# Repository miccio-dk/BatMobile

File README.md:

# BatMobile

Sensors-enabled line-following robot. 
It can be monitored, configured, and controlled remotely using a custom-made Java software (not included in this repository).

Developed as part of a DTU Diplom 4th semester multidisciplinary project.

[Link of test-run video (hosted on YouTube)](http://youtu.be/BTn029kNY_Q)

## Installation

1. Print the PCBs (a breadboard will do too)
2. Cut the chassis pieces
3. Upload the code
4. Assemble everything
5. Run!

## Usage

TODO: Write usage instructions

## Contributing

1. Fork it!
2. Create your feature branch: `git checkout -b my-new-feature`
3. Commit your changes: `git commit -am 'Add some feature'`
4. Push to the branch: `git push origin my-new-feature`
5. Submit a pull request :D

## History

TODO: Write history

## License

Code released under the terms of GPL v3 or higher.

Other documentation licensed under Creative Commons (BY-NC-ND v3).

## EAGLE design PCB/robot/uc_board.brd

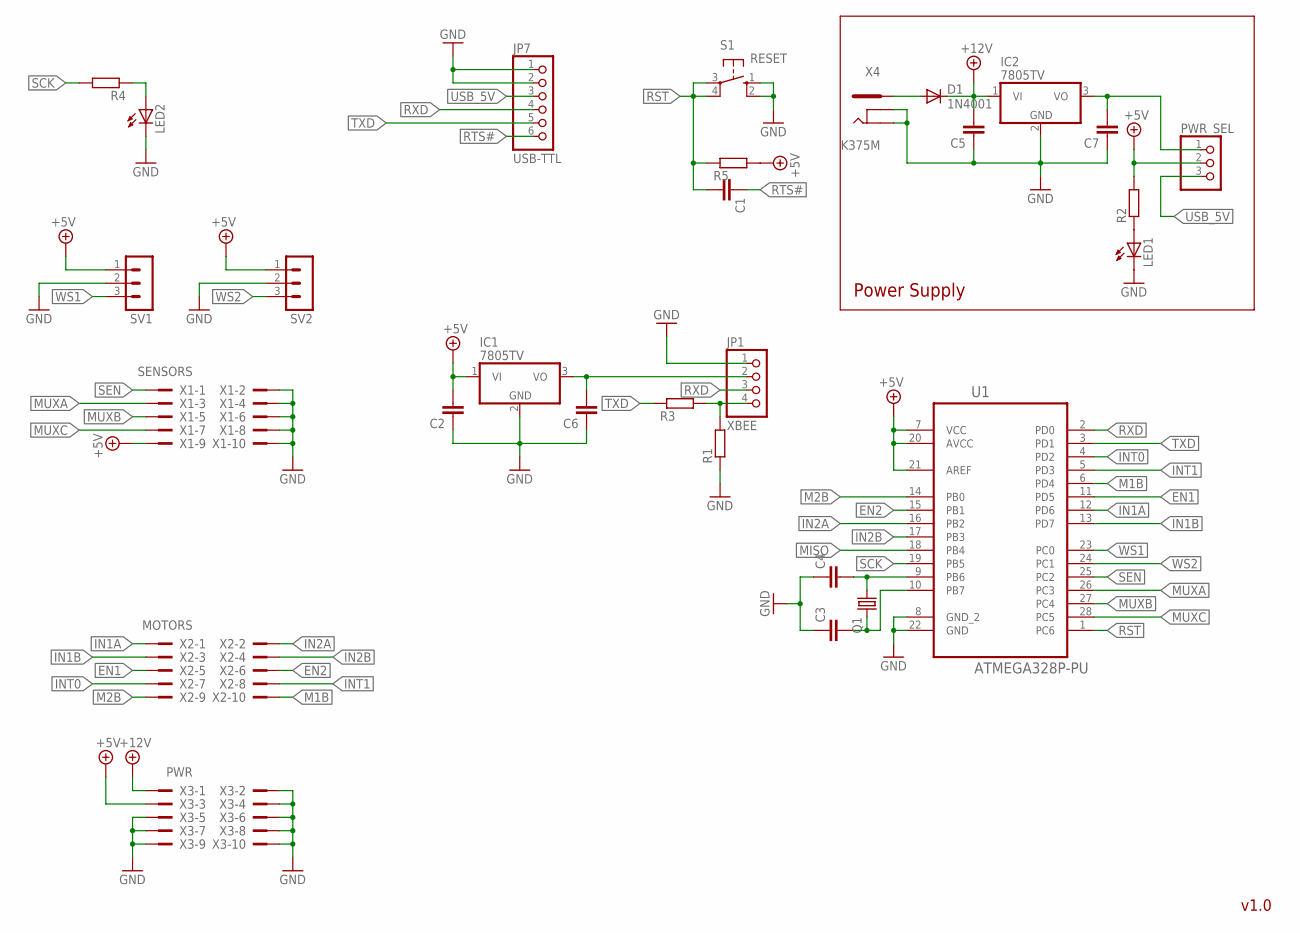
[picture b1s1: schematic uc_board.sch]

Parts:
C1: C-EU050-025X075; C050-025X075
C2, C5, C6, C7: C-EU025-050X050; C025-050X050
C3, C4: C-EU050-024X044; C050-024X044
D1: 1N4001; DO41-10
IC1, IC2: 7805TV; TO220V
JP1: XBEE; 1X04/90
JP7: USB-TTL; 1X06/90
LED1, LED2: LED5MM
PWR_SEL: PINHD-1X3; 1X03
Q1: CRYSTALHC49S; HC49/S
R1, R2, R3, R4, R5: R-EU_0207/10; 0207/10
S1: RESET; B3F-10XX
SV1, SV2: MA03-1
U1: ATMEGA328P-PU; DIP254P762X457-28
X1: SENSORS; PAK100/2500-10
X2: MOTORS; PAK100/2500-10
X3: PWR; PAK100/2500-10
X4: K375M

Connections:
+5V: C2.2, IC1.1 (VI), PWR_SEL.2, R2.2, R5.2, SV1.1, SV2.1, U1.7 (VCC), U1.20 (AVCC), U1.21 (AREF), X1.9, X3.3
+12V: C5.2, D1.C, IC2.1 (VI), X3.1
EN1: U1.11 (PD5), X2.5
EN2: U1.15 (PB1), X2.6
GND: C2.1, C3.1, C4.1, C5.1, C6.1, C7.1, IC1.2 (GND), IC2.2 (GND), JP1.1, JP7.1, JP7.2, LED1.K (C), LED2.K (C), R1.1, S1.1 (S), S1.2 (S1), SV1.2, SV2.2, U1.8 (GND_2), U1.22 (GND), X1.2, X1.4, X1.6, X1.8, X1.10, X3.2, X3.4, X3.5, X3.6, X3.7, X3.8, X3.9, X3.10, X4.2, X4.3
IN1A: U1.12 (PD6), X2.1
IN1B: U1.13 (PD7), X2.3
IN2A: U1.16 (PB2), X2.2
IN2B: U1.17 (PB3), X2.4
INT0: U1.4 (PD2), X2.7
INT1: U1.5 (PD3), X2.8
M1B: U1.6 (PD4), X2.10
M2B: U1.14 (PB0), X2.9
MISO: U1.18 (PB4)
MUXA: U1.26 (PC3), X1.3
MUXB: U1.27 (PC4), X1.5
MUXC: U1.28 (PC5), X1.7
unnamed: C4.2, Q1.1, U1.9 (PB6)
unnamed: C3.2, Q1.2, U1.10 (PB7)
unnamed: LED1.A, R2.1
unnamed: LED2.A, R4.1
unnamed: C6.2, IC1.3 (VO), JP1.2
unnamed: JP1.4, R1.2, R3.2
unnamed: D1.A, X4.1
unnamed: C7.2, IC2.3 (VO), PWR_SEL.1
RST: C1.2, R5.1, S1.3, S1.4 (P1), U1.1 (PC6)
RTS#: C1.1, JP7.6
RXD: JP1.3, JP7.4, U1.2 (PD0)
SCK: R4.2, U1.19 (PB5)
SEN: U1.25 (PC2), X1.1
TXD: JP7.5, R3.1, U1.3 (PD1)
USB_5V: JP7.3, PWR_SEL.3
WS1: SV1.3, U1.23 (PC0)
WS2: SV2.3, U1.24 (PC1)

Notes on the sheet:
Power Supply
v1.0

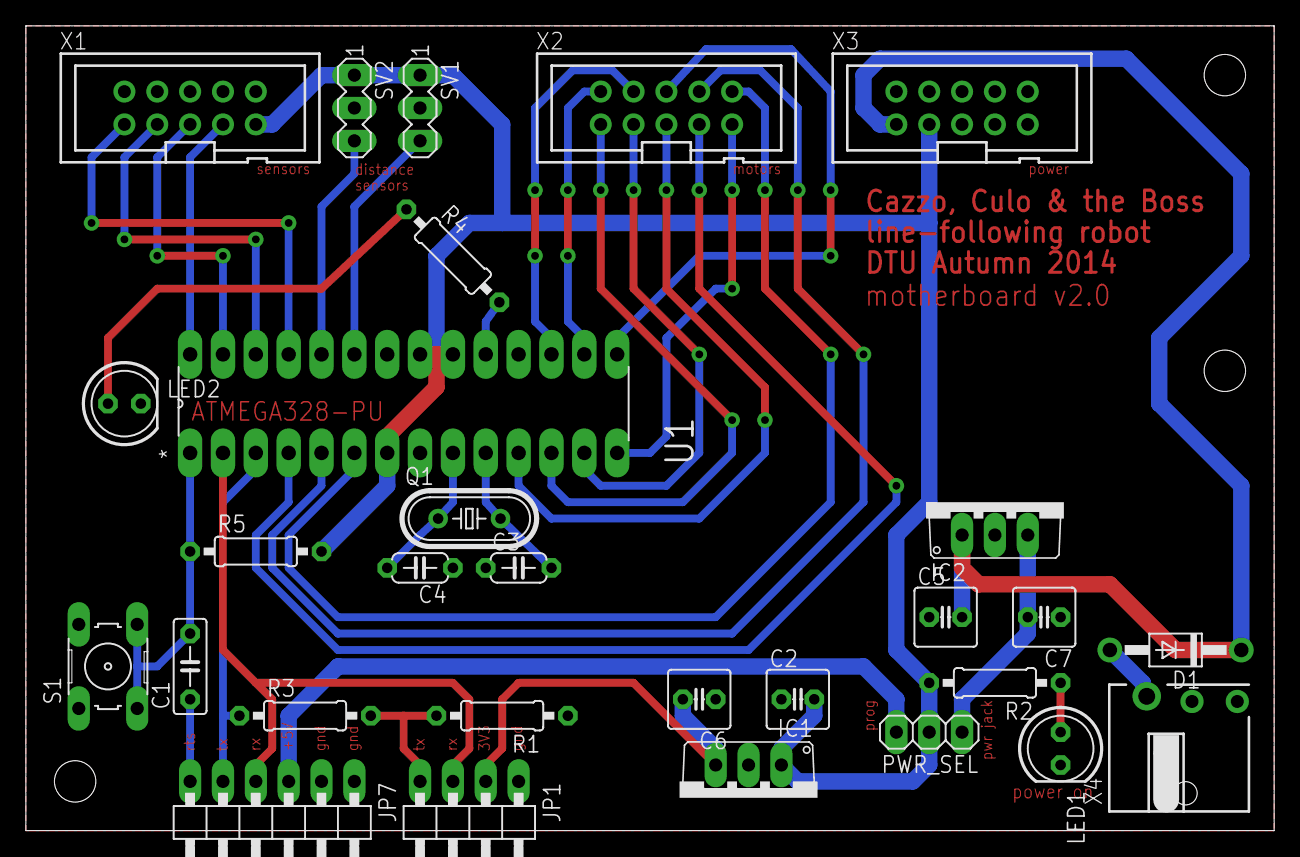
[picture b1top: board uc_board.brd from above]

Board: 2 copper layers, 96.5 x 62.2 mm, 29 parts (0 on the bottom side), 33 nets.

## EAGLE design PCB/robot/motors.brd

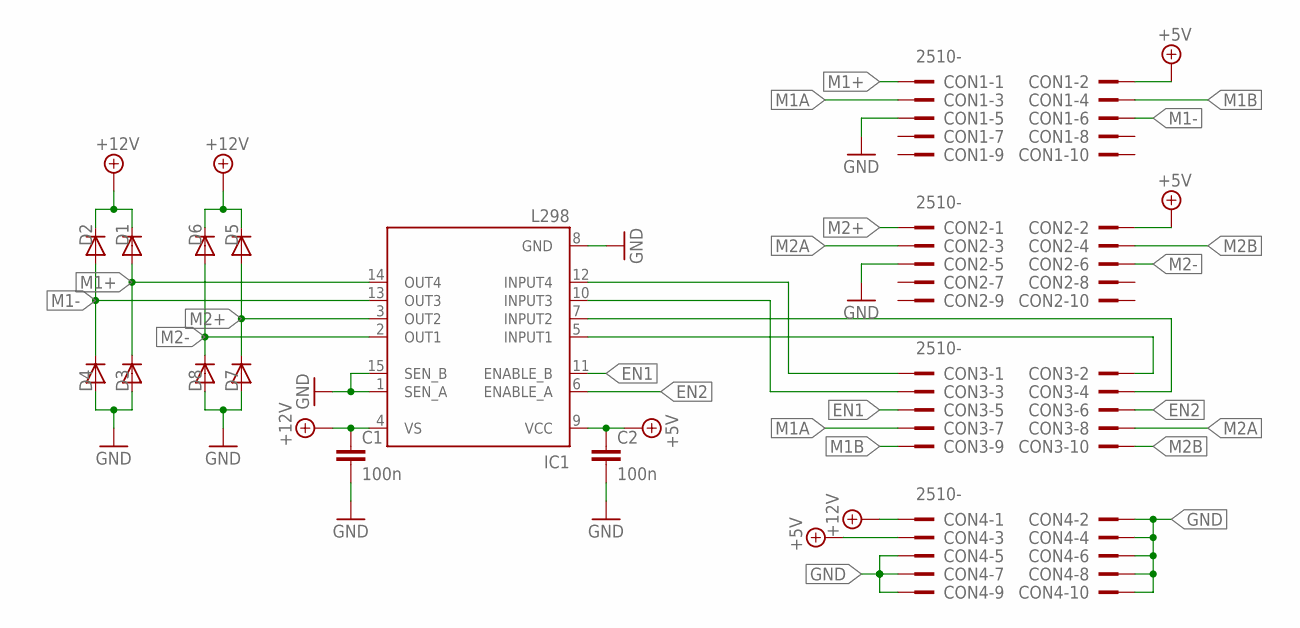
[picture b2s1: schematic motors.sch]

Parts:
C1, C2: 100n; C050-025X075
CON1, CON2, CON3, CON4: 2510-; PAK100/2500-10
D1, D2, D3, D4, D5, D6, D7, D8: 1N4004; DO41-10
IC1: L298; MULTIWATT-15

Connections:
+5V: C2.1, CON1.2, CON2.2, CON4.3, IC1.9 (VCC)
+12V: C1.1, CON4.1, D1.C, D2.C, D5.C, D6.C, IC1.4 (VS)
EN1: CON3.5, IC1.11 (ENABLE_B)
EN2: CON3.6, IC1.6 (ENABLE_A)
GND: C1.2, C2.2, CON1.5, CON2.5, CON4.2, CON4.4, CON4.5, CON4.6, CON4.7, CON4.8, CON4.9, CON4.10, D3.A, D4.A, D7.A, D8.A, IC1.1 (SEN_A), IC1.8 (GND), IC1.15 (SEN_B)
M1+: CON1.1, D1.A, D3.C, IC1.14 (OUT4)
M1-: CON1.6, D2.A, D4.C, IC1.13 (OUT3)
M1A: CON1.3, CON3.7
M1B: CON1.4, CON3.9
M2+: CON2.1, D5.A, D7.C, IC1.3 (OUT2)
M2-: CON2.6, D6.A, D8.C, IC1.2 (OUT1)
M2A: CON2.3, CON3.8
M2B: CON2.4, CON3.10
unnamed: CON3.3, IC1.10 (INPUT3)
unnamed: CON3.2, IC1.5 (INPUT1)
unnamed: CON3.1, IC1.12 (INPUT4)
unnamed: CON3.4, IC1.7 (INPUT2)

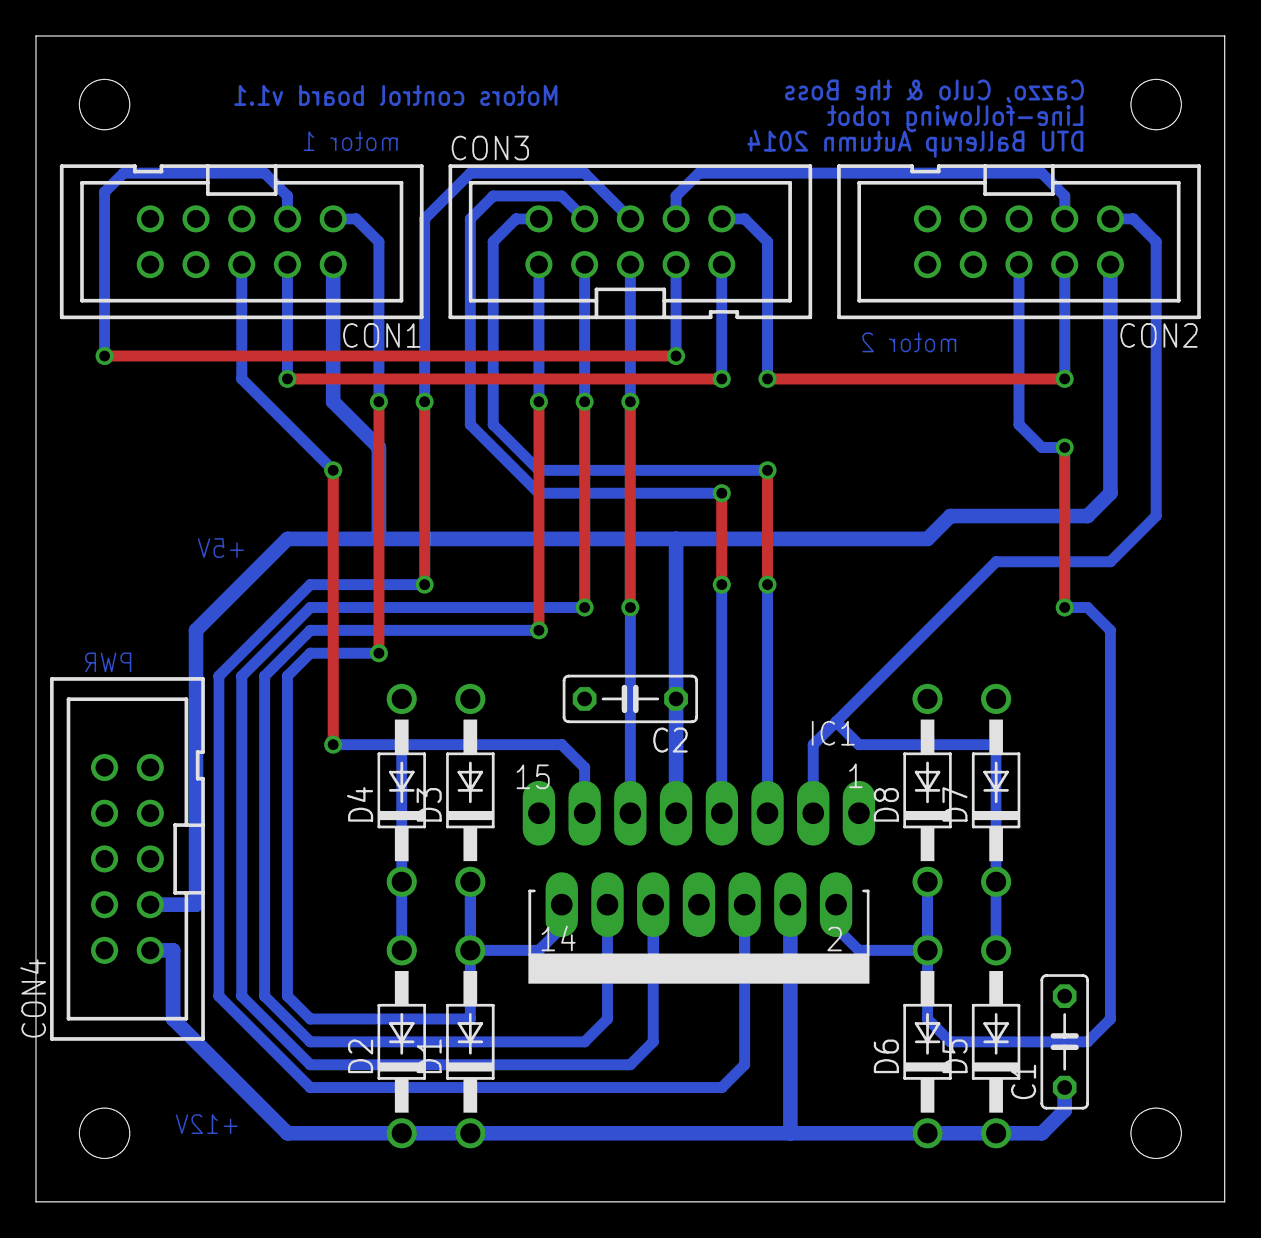
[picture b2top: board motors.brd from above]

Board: 2 copper layers, 66.0 x 64.8 mm, 15 parts (0 on the bottom side), 17 nets.

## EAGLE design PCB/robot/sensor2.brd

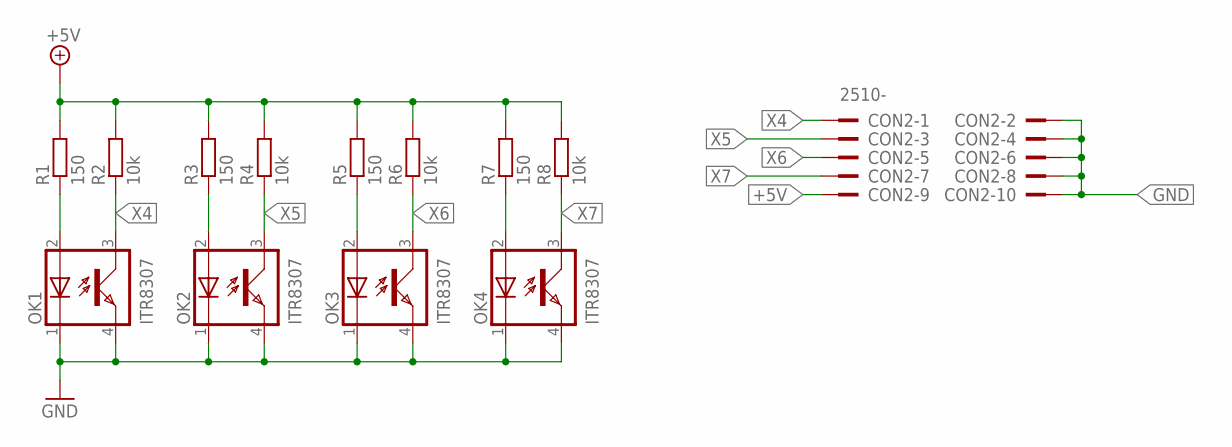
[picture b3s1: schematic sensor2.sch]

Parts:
CON2: 2510-; PAK100/2500-10
OK1, OK2, OK3, OK4: ITR8307; F43
R1, R3, R5, R7: 150; 0204/7
R2, R4, R6, R8: 10k; 0204/7

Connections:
+5V: CON2.9, R1.2, R2.2, R3.2, R4.2, R5.2, R6.2, R7.2, R8.2
GND: CON2.2, CON2.4, CON2.6, CON2.8, CON2.10, OK1.1 (C), OK1.4 (EMIT), OK2.1 (C), OK2.4 (EMIT), OK3.1 (C), OK3.4 (EMIT), OK4.1 (C), OK4.4 (EMIT)
unnamed: OK1.2 (A), R1.1
unnamed: OK2.2 (A), R3.1
unnamed: OK3.2 (A), R5.1
unnamed: OK4.2 (A), R7.1
X4: CON2.1, OK1.3 (COL), R2.1
X5: CON2.3, OK2.3 (COL), R4.1
X6: CON2.5, OK3.3 (COL), R6.1
X7: CON2.7, OK4.3 (COL), R8.1

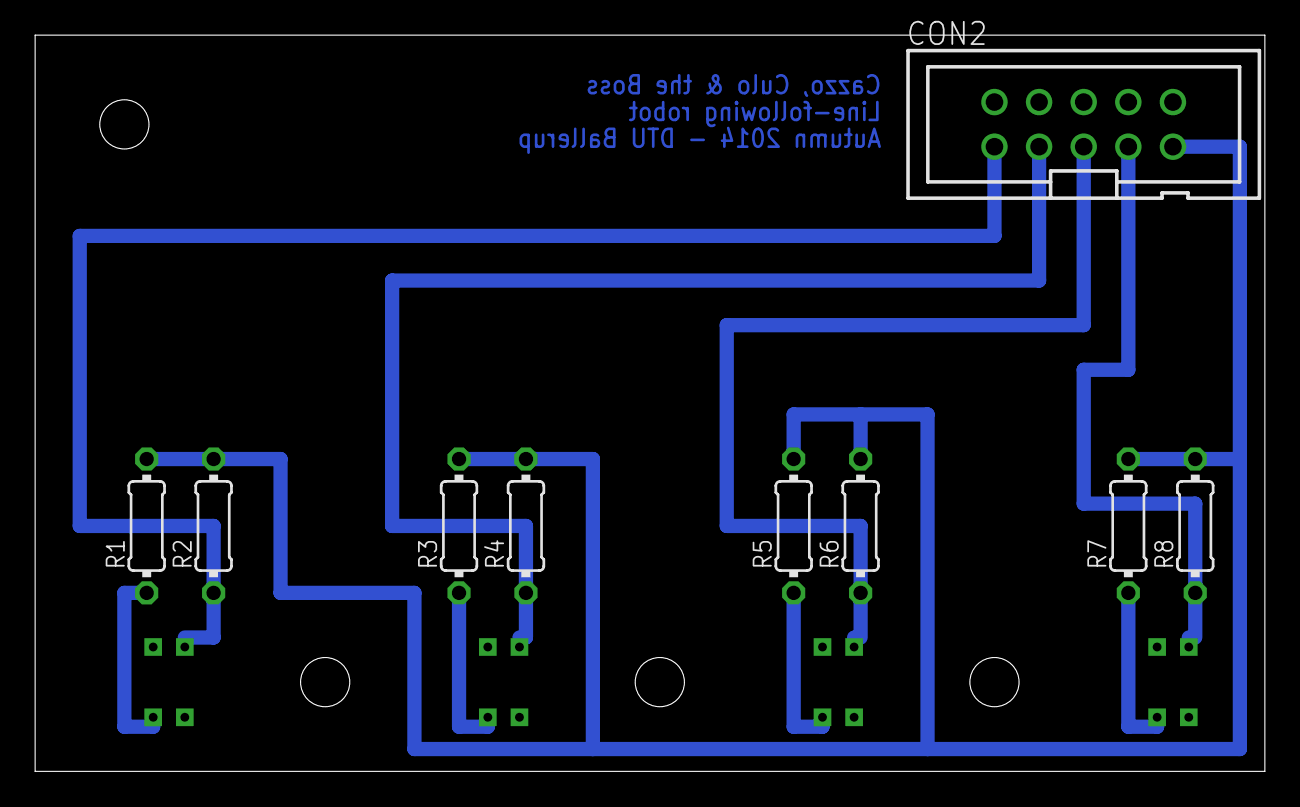
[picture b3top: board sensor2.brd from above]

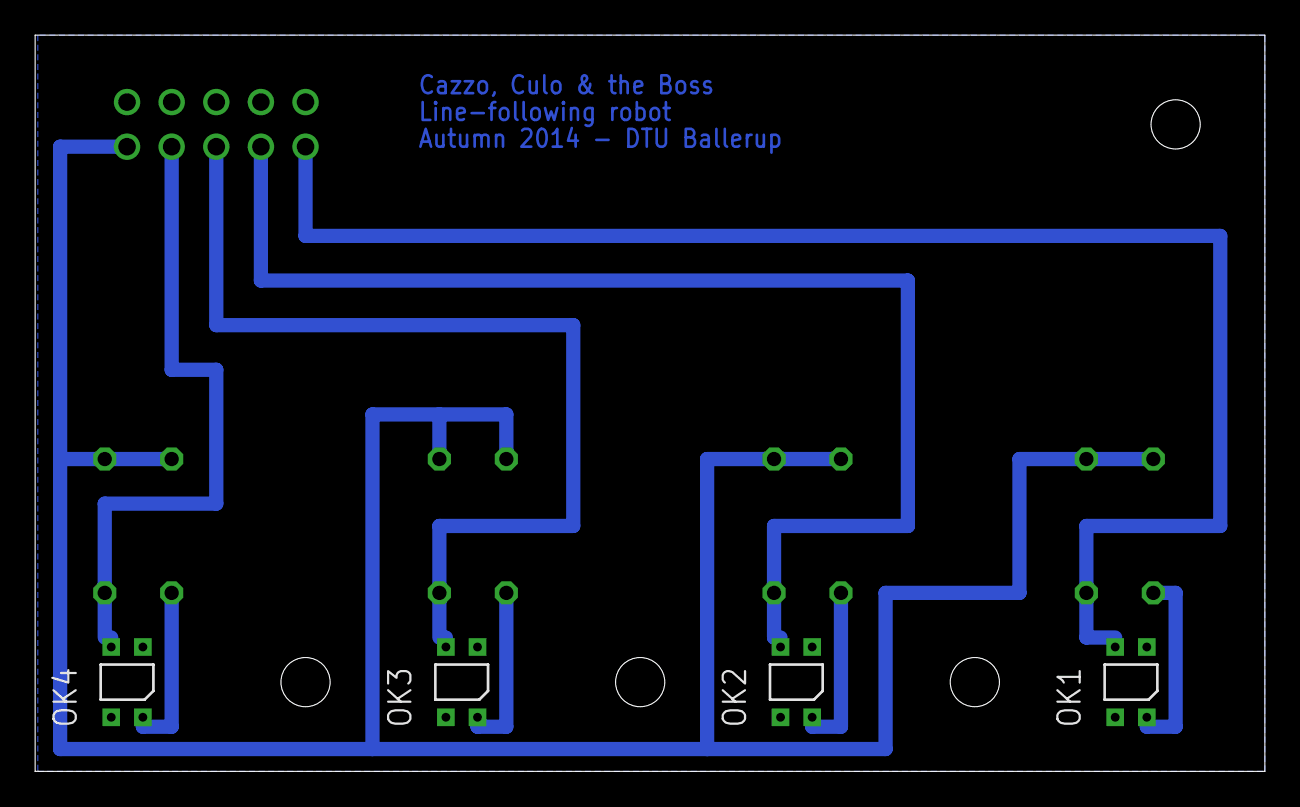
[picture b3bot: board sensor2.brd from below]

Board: 2 copper layers, 70.0 x 41.9 mm, 13 parts (4 on the bottom side), 10 nets.

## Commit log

2015-02-28 project files
